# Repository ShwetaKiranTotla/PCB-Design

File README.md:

# PCB-Design
I had attended a course "Design with KiCAD" (By Wissam Botros) on Udemy from which I learnt the know-hows of PCB Design. This repository contains source files for the open-source projects I have designed along with other finished PCBs I have built.

#
3D model of a Motor Controller board for DC and stepper motors based on the L298 driver module. It can drive two 3-30V DC motors and is capable of 2A continuous current per channel. 

#
Power Supply module for an Electric Vehicle  

#
Servo Control Card for an Aerospace application that independently controls six servo motor driven by PWM signals from micrcontroller and receives analog feedback.

#
Schematic of the L298 Motor Controller Board.

PCB Design of the Motor Controller board

Back view of the Motor Controller PCB  

#
A three phase level shifter PCB to drive a three phase six signal load from PWM signals generated by micrcontroller.

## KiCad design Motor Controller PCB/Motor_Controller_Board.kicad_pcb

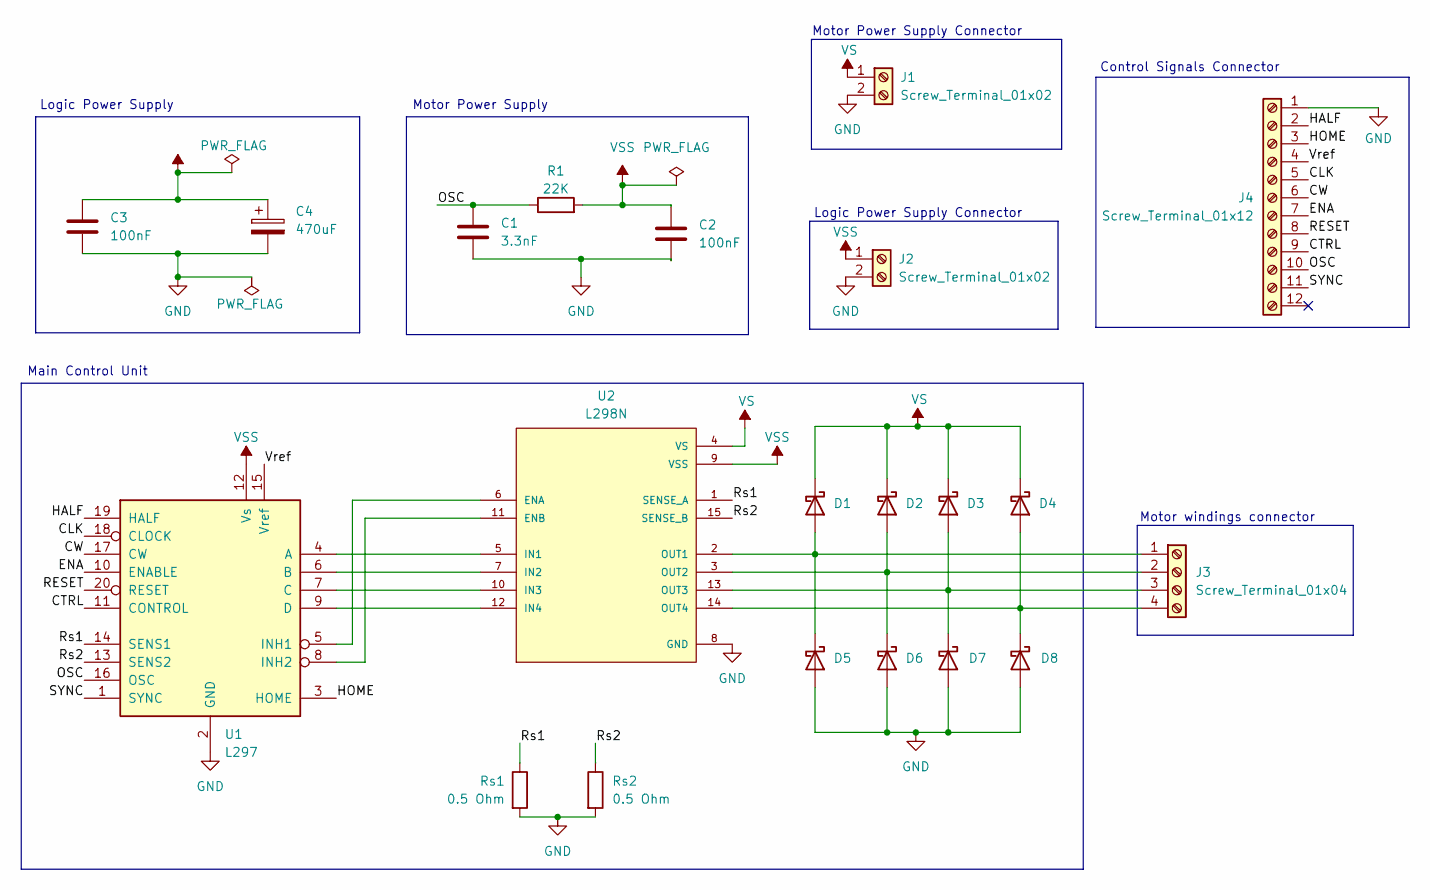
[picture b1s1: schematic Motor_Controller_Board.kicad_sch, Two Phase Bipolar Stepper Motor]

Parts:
C1: 3.3nF; C_Rect_L10.0mm_W3.0mm_P7.50mm_FKS3_FKP3
C2, C3: 100nF; C_Rect_L7.5mm_W6.5mm_P5.00mm
C4: 470uF; CP_Radial_D13.0mm_P5.00mm
D1, D2, D3, D4, D5, D6, D7, D8: D_Schottky; D_DO-27_P15.24mm_Horizontal
J1, J2: Screw_Terminal_01x02; TerminalBlock_Phoenix_MKDS-1,5-2-5.08_1x02_P5.08mm_Horizont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
J3: Screw_Terminal_01x04; TerminalBlock_Phoenix_MKDS-1,5-4_1x04_P5.00mm_Horizontal
J4: Screw_Terminal_01x12; TerminalBlock_Phoenix_MKDS-1,5-12_1x12_P5.00mm_Horizontal
R1: 22K; R_Axial_DIN0922_L20.0mm_D9.0mm_P25.40mm_Horizontal
Rs1, Rs2: 0.5 Ohm; R_Axial_DIN0414_L11.9mm_D4.5mm_P15.24mm_Horizontal
U1: L297; DIP-20_W7.62mm_LongPads
U2: L298N; TO127P2020X500X2100-15; DigiKey_Part_Number 497-1395-5-ND

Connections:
/CLK: J4.5, U1.18 (CLOCK)
/CTRL: J4.9, U1.11 (CONTROL)
/CW: J4.6, U1.17 (CW)
/ENA: J4.7, U1.10 (ENABLE)
/HALF: J4.2, U1.19 (HALF)
/HOME: J4.3, U1.3 (HOME)
/OSC: C1.1, J4.10, R1.1, U1.16 (OSC)
/RESET: J4.8, U1.20 (RESET)
/Rs1: Rs1.1, U1.14 (SENS1), U2.1 (SENSE_A)
/Rs2: Rs2.1, U1.13 (SENS2), U2.15 (SENSE_B)
/SYNC: J4.11, U1.1 (SYNC)
/Vref: J4.4, U1.15 (Vref)
GND: C1.2, C2.2, C3.2, C4.2, D5.2 (A), D6.2 (A), D7.2 (A), D8.2 (A), J1.2, J2.2, J4.1, Rs1.2, Rs2.2, U1.2 (GND), U2.8 (GND)
unnamed: D1.2 (A), D5.1 (K), J3.1, U2.2 (OUT1)
unnamed: D2.2 (A), D6.1 (K), J3.2, U2.3 (OUT2)
unnamed: D3.2 (A), D7.1 (K), J3.3, U2.13 (OUT3)
unnamed: D4.2 (A), D8.1 (K), J3.4, U2.14 (OUT4)
unnamed: U1.4 (A), U2.5 (IN1)
unnamed: U1.6 (B), U2.7 (IN2)
unnamed: U1.7 (C), U2.10 (IN3)
unnamed: U1.9 (D), U2.12 (IN4)
unnamed: U1.5 (INH1), U2.6 (ENA)
unnamed: U1.8 (INH2), U2.11 (ENB)
VS: C3.1, C4.1, D1.1 (K), D2.1 (K), D3.1 (K), D4.1 (K), J1.1, U2.4 (VS)
VSS: C2.1, J2.1, R1.2, U1.12 (Vs), U2.9 (VSS)

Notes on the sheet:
Logic Power Supply Connector
Main Control Unit
Motor Power Supply Connector
Logic Power Supply
Control Signals Connector
Motor windings connector
Motor Power Supply

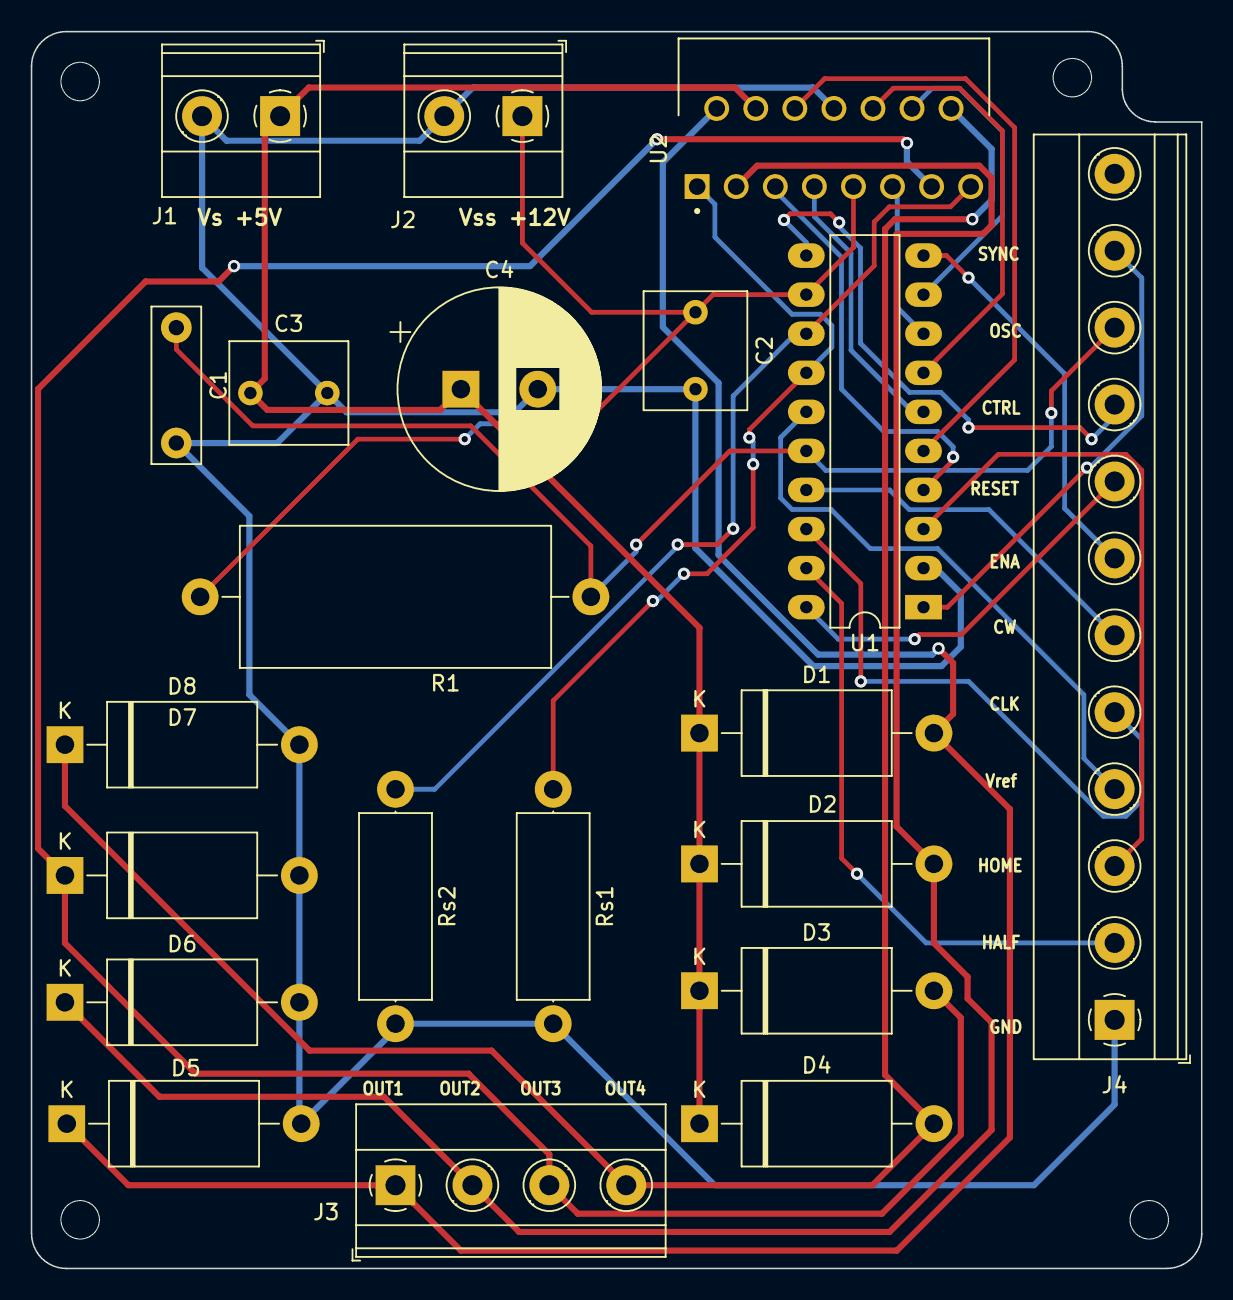
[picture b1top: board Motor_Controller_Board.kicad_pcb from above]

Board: 2 copper layers, 76.1 x 80.4 mm, 21 parts (0 on the bottom side), 25 nets.

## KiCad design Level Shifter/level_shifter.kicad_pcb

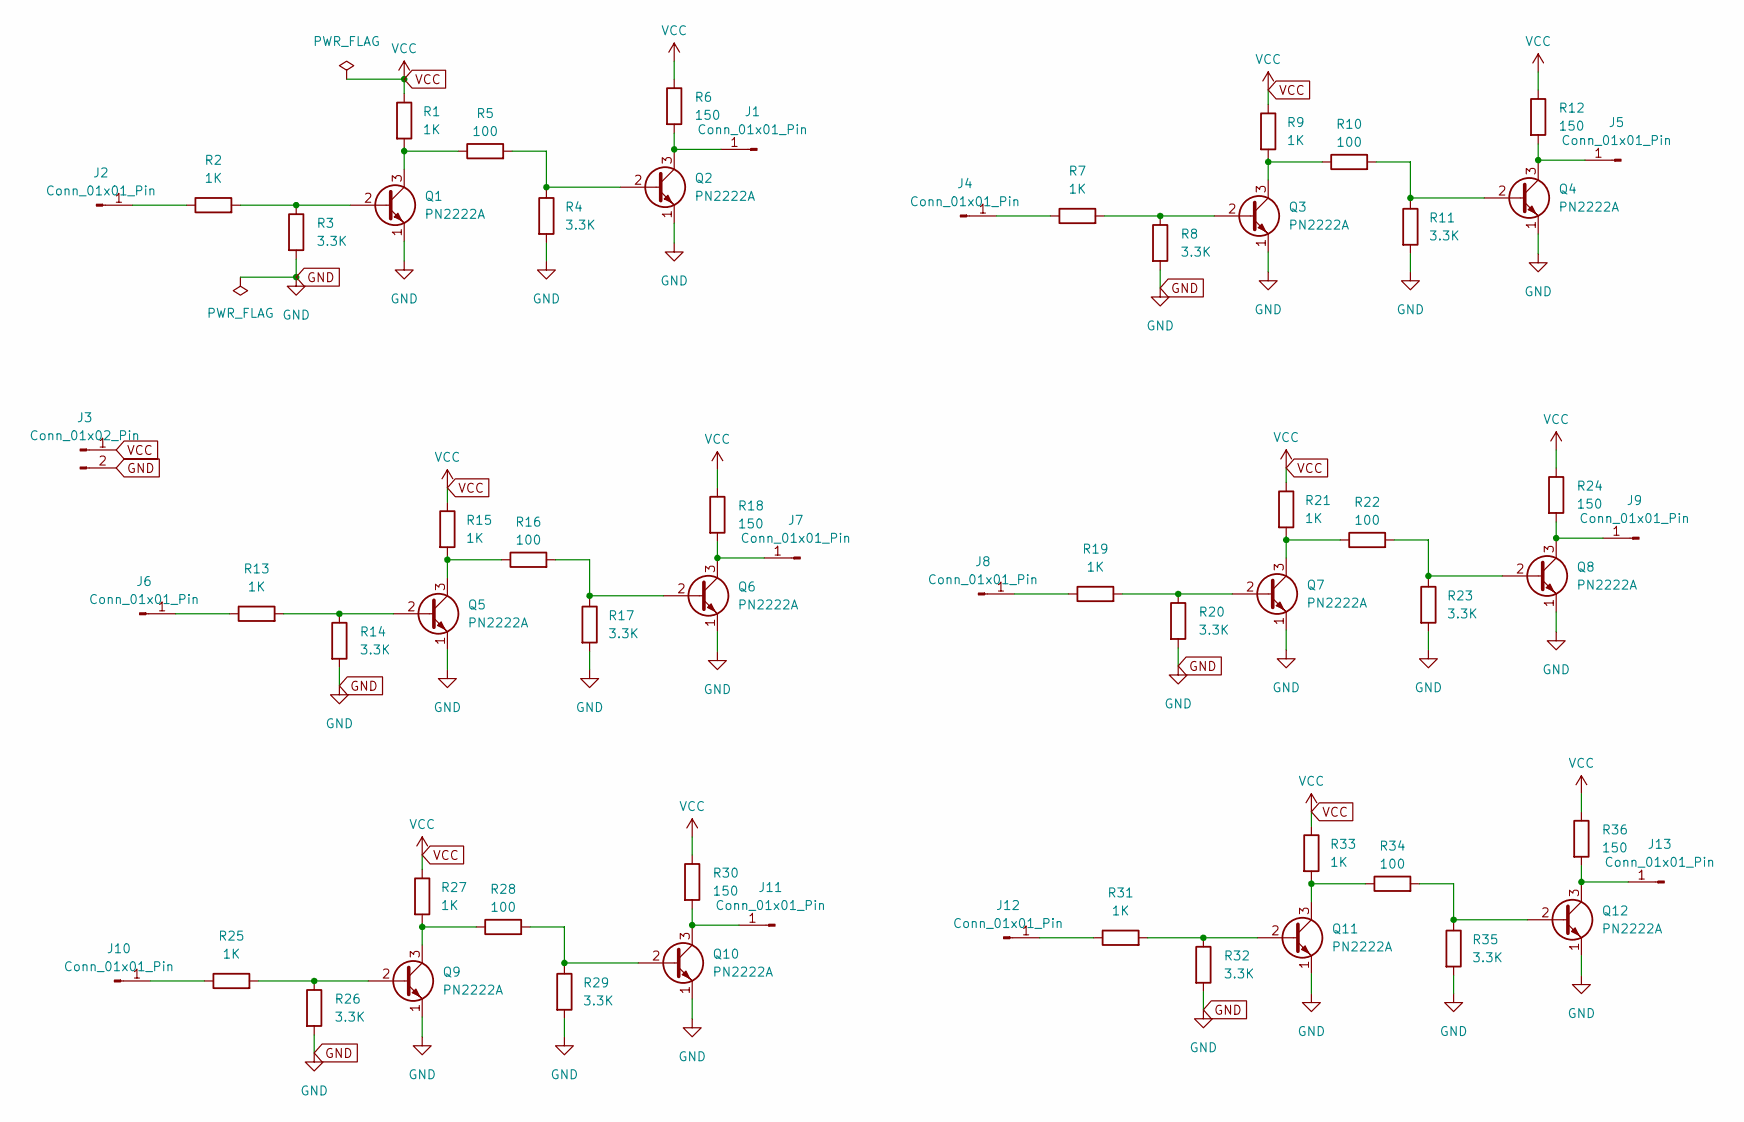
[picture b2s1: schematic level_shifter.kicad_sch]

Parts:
J1, J2, J4, J5, J6, J7, J8, J9, J10, J11, J12, J13: Conn_01x01_Pin; PinHeader_1x01_P2.54mm_Horizontal
J3: Conn_01x02_Pin; PinHeader_1x02_P2.54mm_Vertical
Q1, Q2, Q3, Q4, Q5, Q6, Q7, Q8, Q9, Q10, Q11, Q12: PN2222A; TO-92_Inline
R1, R2, R7, R9, R13, R15, R19, R21, R25, R27, R31, R33: 1K; R_0603_1608Metric
R3, R4, R8, R11, R14, R17, R20, R23, R26, R29, R32, R35: 3.3K; R_0603_1608Metric
R5, R10, R16, R22, R28, R34: 100; R_0603_1608Metric
R6, R12, R18, R24, R30, R36: 150; R_0603_1608Metric

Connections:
GND: J3.2, Q1.1 (E), Q2.1 (E), Q3.1 (E), Q4.1 (E), Q5.1 (E), Q6.1 (E), Q7.1 (E), Q8.1 (E), Q9.1 (E), Q10.1 (E), Q11.1 (E), Q12.1 (E), R3.2, R4.2, R8.2, R11.2, R14.2, R17.2, R20.2, R23.2, R26.2, R29.2, R32.2, R35.2
unnamed: J1.1, Q2.3 (C), R6.2
unnamed: J2.1, R2.1
unnamed: J4.1, R7.1
unnamed: J5.1, Q4.3 (C), R12.2
unnamed: J6.1, R13.1
unnamed: J7.1, Q6.3 (C), R18.2
unnamed: J8.1, R19.1
unnamed: J9.1, Q8.3 (C), R24.2
unnamed: J10.1, R25.1
unnamed: J11.1, Q10.3 (C), R30.2
unnamed: J12.1, R31.1
unnamed: J13.1, Q12.3 (C), R36.2
unnamed: Q1.2 (B), R2.2, R3.1
unnamed: Q1.3 (C), R1.2, R5.1
unnamed: Q2.2 (B), R4.1, R5.2
unnamed: Q3.2 (B), R7.2, R8.1
unnamed: Q3.3 (C), R9.2, R10.1
unnamed: Q4.2 (B), R10.2, R11.1
unnamed: Q5.2 (B), R13.2, R14.1
unnamed: Q5.3 (C), R15.2, R16.1
unnamed: Q6.2 (B), R16.2, R17.1
unnamed: Q7.2 (B), R19.2, R20.1
unnamed: Q7.3 (C), R21.2, R22.1
unnamed: Q8.2 (B), R22.2, R23.1
unnamed: Q9.2 (B), R25.2, R26.1
unnamed: Q9.3 (C), R27.2, R28.1
unnamed: Q10.2 (B), R28.2, R29.1
unnamed: Q11.2 (B), R31.2, R32.1
unnamed: Q11.3 (C), R33.2, R34.1
unnamed: Q12.2 (B), R34.2, R35.1
VCC: J3.1, R1.1, R6.1, R9.1, R12.1, R15.1, R18.1, R21.1, R24.1, R27.1, R30.1, R33.1, R36.1

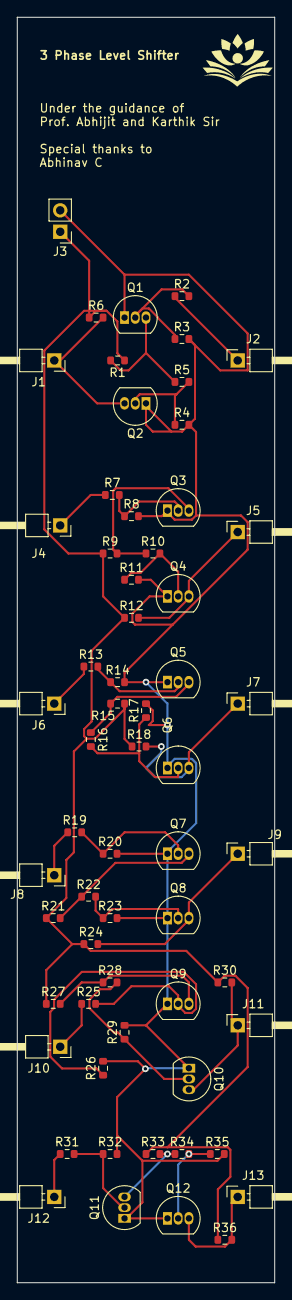
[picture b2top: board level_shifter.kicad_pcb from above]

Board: 2 copper layers, 30.5 x 149.9 mm, 61 parts (0 on the bottom side), 32 nets.

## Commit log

2024-03-16 PCB Project Details
2024-03-16 Added PCB Project files.
2024-03-16 Level Shifter
2024-03-16 Motor Controller PCB
2024-03-16 Added source files
2024-03-16 Added level shifter
